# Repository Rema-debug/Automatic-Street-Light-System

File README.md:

# Automatic-Street-Light-System

Project Overview
The Automatic Street Light System is a smart embedded system designed to automatically control street lighting based on environmental light conditions and motion detection.
The system improves energy efficiency, reduces power wastage, and minimizes manual operation of street lights.
This project was developed as part of the ICT 215 – Robotics and Embedded Systems Course.

Project Objectives
1. Design an intelligent street lighting system.
2. Automatically switch street lights ON at night and OFF during the day.
3. Reduce energy consumption using sensor-based automation.
4. Simulate the system before hardware implementation.
5. Design and implement a custom Printed Circuit Board (PCB).
6. Develop Arduino-based control logic.

System Components
Hardware Components:
1. Arduino Uno (Microcontroller)
2. Light Dependent Resistor (LDR)
3. Passive Infrared (PIR) Motion Sensor
4. LED Street Light
5. Resistors and Capacitors
6. Transistor / Relay Module
7. Solar Panel (Power Source)
8. Power Supply Unit

Software & Tools Used
1. Arduino IDE – Programming and firmware development
2. Proteus – Circuit simulation
3. Tinkercad – 3D circuit visualization and testing
4. KiCad – PCB schematic and layout design
5. GitHub – Project documentation and version control

System Working Principle
1. The LDR sensor detects ambient light intensity.
2. During daylight, the street light remains OFF.
3. When darkness is detected, the system automatically turns the light ON.
4. The PIR sensor detects motion at night.
5. Light brightness increases only when movement is detected, helping to conserve energy.
6. The Arduino microcontroller processes sensor data and controls the lighting system.

System Block Diagram

LDR Sensor + PIR Sensor
          ↓
     Arduino Uno
          ↓
   Switching Circuit
          ↓
      LED Street Light

Simulation
The circuit was first tested using:
1. Proteus simulation environment
2. Tinkercad virtual prototyping
This helped verify system functionality before hardware implementation.

PCB Design
A custom PCB was designed using KiCad to:
1. Improve circuit reliability
2. Reduce wiring complexity
3. Create a compact and professional hardware layout

Results
1. Reliable automatic switching achieved.
2. Response time: approximately 3–4 seconds.
3. Stable operation during repeated ON/OFF cycles.
4. Significant reduction in unnecessary energy usage.

Future Improvements
1. IoT-based remote monitoring
2. GSM/WiFi fault reporting
3. Smart city integration
4. Adaptive brightness control
5. Weather-resistant outdoor deployment

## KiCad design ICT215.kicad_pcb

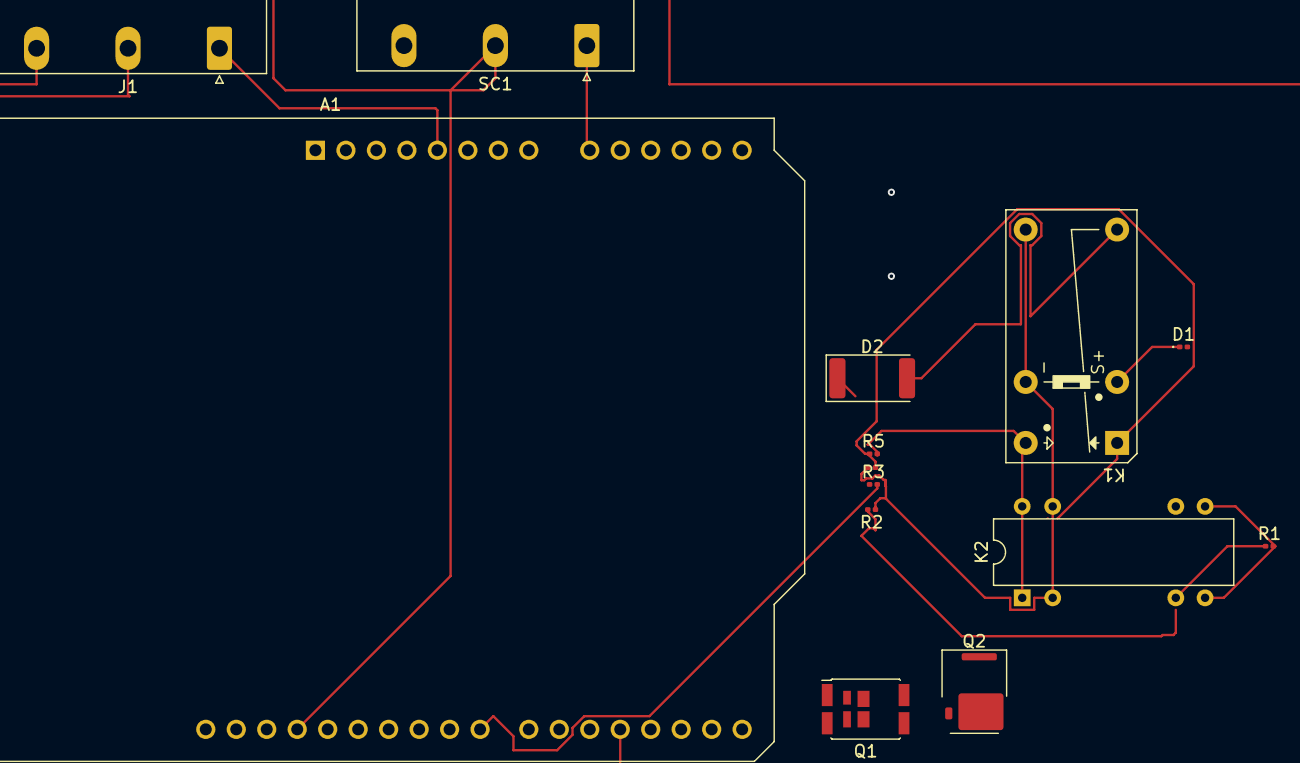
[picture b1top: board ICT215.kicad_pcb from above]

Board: 2 copper layers, 15 parts (0 on the bottom side), 12 nets.

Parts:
A1: Arduino_UNO_R3
BT1: Battery; Battery_CR1225
D1: D; D_0201_0603Metric
D2: LED; LED_2512_6332Metric
J1: Conn_01x03_Pin; PhoenixContact_GMSTBA_2,5_3-G-7,62_1x03_P7.62mm_Horizontal
K1: DR-24V; Relay_SPDT_Panasonic_DR
K2: DIPxx-1Axx-12xD; Relay_StandexMeder_DIP_LowProfile
Q1: Q_NMOS; DirectFET_MF
Q2: Q_NPN; GaN_Systems_GaNPX-3_5x6.6mm_Drain2.93x0.6mm
R1, R2, R3, R4, R5: R; R_0201_0603Metric
SC1: Solar_Cell; PhoenixContact_GMSTBA_2,5_3-G-7,62_1x03_P7.62mm_Horizontal

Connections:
GND: D2.1 (K), K1.A2, K1.PE (Earth), K2.2, K2.13, R2.1, R4.2
unnamed: A1.5 (+5V), J1.1
unnamed: A1.9 (A0), SC1.1 (+)
unnamed: A1.19 (D4), J1.2
unnamed: A1.23 (D8), R3.2
unnamed: K2.7, K2.8, R1.2
unnamed: D1.1 (K), K1.A1
unnamed: D2.2 (A), K1.11
unnamed: A1.29 (GND), J1.3, SC1.2 (-)
unnamed: K1.12, R4.1, R5.1
unnamed: K1.14, K2.1, K2.14, R5.2
unnamed: K2.6, R1.1, R2.2
